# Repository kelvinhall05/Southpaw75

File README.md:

# Southpaw75

The Southpaw75 is a budget FR4 keyboard designed to make a southpaw-style layout available to everyone with as few compromises as possible.

### Disclaimer: You must follow this guide in the order it is written. Assembling stuff in the wrong order (specifically your Pro Micro or Elite C and its headers) will likely result in you having to desolder components and significantly increase the amount of time it takes to assemble. I am not responsible for boards damaged during assembly. I highly recommend you read through the entire guide before starting assembly.

### Please also note that the pictures in this guide were mostly taken after I had already assembled a prototype, and I did not have enough diodes or any switches to fully assemble another board. Please only use the pictures in this guide as a reference for the step they follow and not as the guide itself.

# Assembly:
### This is what the back of an empty PCB looks like (please note, the GB version has some minor changes):

### 1. Bend the legs of all your diodes so they look like this:

### 2. Put the diodes through the PCB so the legs stick out the front side of the board and so the diode is flush with the back, making sure the black line on the diode faces the square pad:

### 3. Solder from the back and snip the legs:

### 4. Repeat for all diodes (you will have to solder 78, and you may have several extras). Please note that several diodes have their footprint rotated but are electrically identical, meaning black stripe will still go to square pad.
### 5. Solder your reset button to the PCB (use tweezers to hold it down, as the metal will conduct heat from your iron and burn your finger)
### Note: If you've lost your reset button, don't worry. Shorting the two pads closest to the edge of the PCB or the two closest to the inside will reset your controller. After all, that's all the button does :)
### 6. Place your Pro Micro or Elite C onto its pin headers and sit it into the board so the Pro Micro is on the back of the PCB (the side with the Southpaw logo) and tape it down to temporarily hold it in place. This helps align the pin headers properly. It doesn't matter whether you put the shorter pins on the PCB or the longer ones; either way, you will have to snip the longer ones once you've soldered them in. **DO NOT SOLDER THE PRO MICRO OR ELITE C TO THE PIN HEADERS YET!**

### 7. Solder in the pin headers from the front side of the PCB. **Do not solder the Pro Micro or Elite C yet, just the headers!**

### 8. Attach your stabs to the PCB (some PCB stabs might be a tight fit with the plate; do not be afraid to push, you won't break it)
### 9. Mount switches in the corner of the plate to align it, then lower the plate onto the PCB
### 10. Add the rest of your switches and solder them all in
### 11. Once you have verified that all your diodes, switches, and Pro Micro or Elite C pin headers are soldered properly, you can now solder your Pro Micro or Elite C onto the pin headers:

### Here is what a completed PCB will look like:

### 12. Attach standoffs to the bottom of the plate using screws from the other side
### 13. Screw on the bottom plate
# Flashing instructions for Linux:
### 1. Plug your Pro Micro or Elite C in
### 2. Open up the [QMK configurator](https://config.qmk.fm/#/southpaw75/LAYOUT) and create your desired layout
### 3. Download the .json file (on the left, next to keymap.json)
### 4. Open up a command line
### 5. Type ```qmk flash /path/to/layout.json``` (obviously replacing the file path with the path to your downloaded layout) and follow any additional instructions
### One thing to note is that you can compile a .hex file on the configurator and flash that with avrdude, however, I prefer the method outlined above.
# Flashing instructions for Windows:
### Please keep in mind that I do not run Windows on my own system and cannot 100% verify this flashing procedure will work or if it requires any other configuration. I highly recommend you check the QMK docs if something is not working. I am unable to help with any flashing problems if you run Windows.
### 1. Plug your Pro Micro or Elite C in
### 2. Open up the [QMK configurator](https://config.qmk.fm/#/southpaw75/LAYOUT) and create your desired layout
### 3. Click "compile" in the upper right, and once it's done, download the .hex by clicking "firmware"
### 4. Open up QMK toolbox and load your downloaded .hex
### 5. Click "flash" and follow any additional instructions

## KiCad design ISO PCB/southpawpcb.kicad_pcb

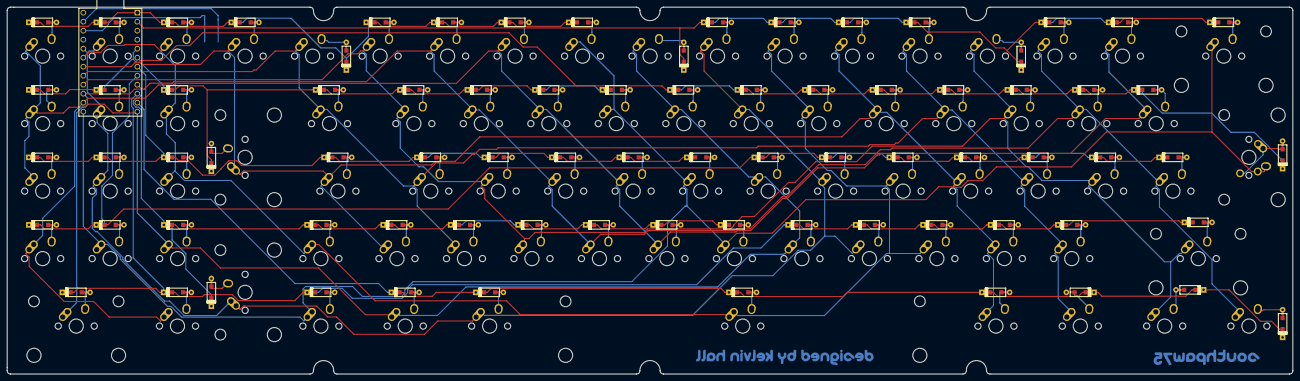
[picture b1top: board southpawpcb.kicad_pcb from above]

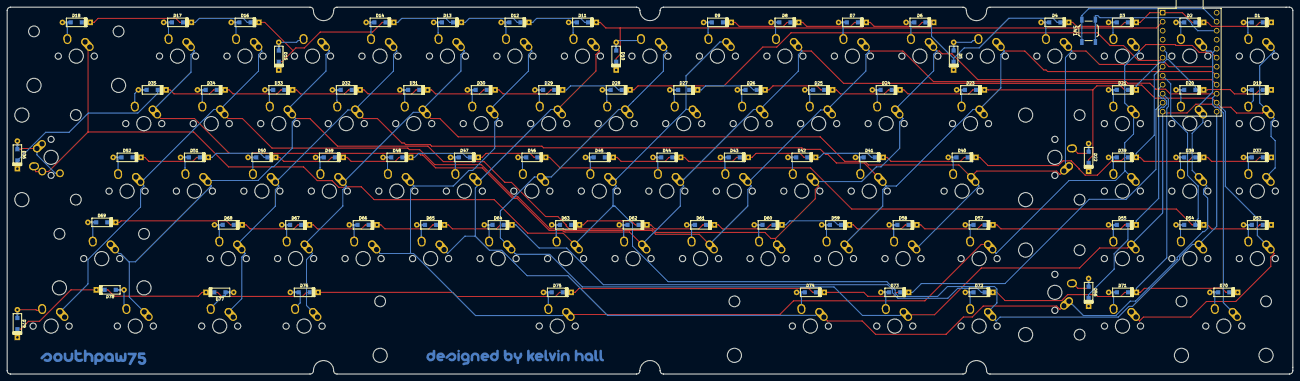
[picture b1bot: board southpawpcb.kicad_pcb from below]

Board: 2 copper layers, 362.9 x 103.6 mm, 164 parts (85 on the bottom side), 99 nets.

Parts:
D1, D2, D3, D4, D5, D6, D7, D8, D9, D10, D11, D12, D13, D14, D15, D16, D17, D18, D19, D20, D21, D22, D23, D24, D25, D26, D27, D28, D29, D30, D31, D32, D33, D34, D35, D36, D37, D38, D39, D40, D41, D42, D43, D44, D45, D46, D47, D48, D49, D50, D51, D52, D53, D54, D55, D56, D57, D58, D59, D60, D61, D62, D63, D64, D65, D66, D67, D68, D69, D70, D71, D72, D73, D74, D75, D76, D77, D78, D79: D; D_SOD123_axial-dual
G1: LOGO; designedbykelvinhallcopy
G2: LOGO; designedbykelvinhall
G3: LOGO; southpaw75smallcopy
G4: LOGO; southpaw75small
K1, K2, K3, K4, K5, K6, K7, K8, K9, K10, K11, K12, K13, K14, K15, K16, K17, K19, K20, K21, K24, K25, K26, K27, K28, K29, K30, K31, K32, K33, K34, K35, K37, K38, K39, K41, K42, K43, K44, K45, K46, K47, K48, K49, K50, K51, K52, K53, K54, K55, K58, K59, K60, K61, K62, K63, K64, K65, K66, K67, K68, K71: KEYSW; MX-1U-NoLED
K18, K22, K56, K70: KEYSW; MX-2U-NoLED
K23: KEYSW; MX-1.5U-NoLED
K36: KEYSW; MX-ISO
K40: KEYSW; MX-1.75U-NoLED
K57, K72, K73, K74, K76, K77, K78, K79: KEYSW; MX-1.25U-NoLED
K69: KEYSW; MX-2.75U-NoLED
K75: KEYSW; MX-6.25U-NoLED
SW1: Reset; SW_SPST_TL3342
U1: ProMicro

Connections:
unnamed: D1.1, D2.1, D3.1, D4.1, D5.1, D6.1, D7.1, D8.1, D9.1, U1.1
unnamed: D1.2, K1.2
unnamed: D2.2, K2.2
unnamed: D3.2, K3.2
unnamed: D4.2, K4.2
unnamed: D5.2, K5.2
unnamed: D6.2, K6.2
unnamed: D7.2, K7.2
unnamed: D8.2, K8.2
unnamed: D9.2, K9.2
unnamed: D10.1, D11.1, D12.1, D13.1, D14.1, D15.1, D16.1, D17.1, D18.1, U1.2
unnamed: D10.2, K10.2
unnamed: D11.2, K11.2
unnamed: D12.2, K12.2
unnamed: D13.2, K13.2
unnamed: D14.2, K14.2
unnamed: D15.2, K15.2
unnamed: D16.2, K16.2
unnamed: D17.2, K17.2
unnamed: D18.2, K18.2
unnamed: D19.1, D20.1, D21.1, D22.1, D23.1, D24.1, D25.1, D26.1, D27.1, U1.5
unnamed: D19.2, K19.2
unnamed: D20.2, K20.2
unnamed: D21.2, K21.2
unnamed: D22.2, K22.2
unnamed: D23.2, K23.2
unnamed: D24.2, K24.2
unnamed: D25.2, K25.2
unnamed: D26.2, K26.2
unnamed: D27.2, K27.2
unnamed: D28.1, D29.1, D30.1, D31.1, D32.1, D33.1, D34.1, D35.1, D36.1, U1.6
unnamed: D28.2, K28.2
unnamed: D29.2, K29.2
unnamed: D30.2, K30.2
unnamed: D31.2, K31.2
unnamed: D32.2, K32.2
unnamed: D33.2, K33.2
unnamed: D34.2, K34.2
unnamed: D35.2, K35.2
unnamed: D36.2, K36.2
unnamed: D37.1, D38.1, D39.1, D40.1, D41.1, D42.1, D43.1, D44.1, D45.1, U1.7
unnamed: D37.2, K37.2
unnamed: D38.2, K38.2
unnamed: D39.2, K39.2
unnamed: D40.2, K40.2
unnamed: D41.2, K41.2
unnamed: D42.2, K42.2
unnamed: D43.2, K43.2
unnamed: D44.2, K44.2
unnamed: D45.2, K45.2
unnamed: D46.1, D47.1, D48.1, D49.1, D50.1, D51.1, D52.1, D53.1, D54.1, U1.8
unnamed: D46.2, K46.2
unnamed: D47.2, K47.2
unnamed: D48.2, K48.2
unnamed: D49.2, K49.2
unnamed: D50.2, K50.2
unnamed: D51.2, K51.2
unnamed: D52.2, K52.2
unnamed: D53.2, K53.2
unnamed: D54.2, K54.2
unnamed: D55.1, D56.1, D57.1, D58.1, D59.1, D60.1, D61.1, D62.1, D63.1, U1.9
unnamed: D55.2, K55.2
unnamed: D56.2, K56.2
unnamed: D57.2, K57.2
unnamed: D58.2, K58.2
unnamed: D59.2, K59.2
unnamed: D60.2, K60.2
unnamed: D61.2, K61.2
unnamed: D62.2, K62.2
unnamed: D63.2, K63.2
unnamed: D64.1, D65.1, D66.1, D67.1, D68.1, D69.1, D70.1, D71.1, D72.1, U1.10
unnamed: D64.2, K64.2
unnamed: D65.2, K65.2
unnamed: D66.2, K66.2
unnamed: D67.2, K67.2
unnamed: D68.2, K68.2
unnamed: D69.2, K69.2
unnamed: D70.2, K70.2
unnamed: D71.2, K71.2
unnamed: D72.2, K72.2
unnamed: D73.1, D74.1, D75.1, D76.1, D77.1, D78.1, D79.1, U1.11
unnamed: D73.2, K73.2
unnamed: D74.2, K74.2
unnamed: D75.2, K75.2
unnamed: D76.2, K76.2
unnamed: D77.2, K77.2
unnamed: D78.2, K78.2
unnamed: D79.2, K79.2
unnamed: K1.1, K10.1, K19.1, K28.1, K37.1, K46.1, K55.1, K64.1, K73.1, U1.12
unnamed: K2.1, K11.1, K20.1, K29.1, K38.1, K47.1, K56.1, K65.1, K74.1, U1.20
unnamed: K3.1, K12.1, K21.1, K30.1, K39.1, K48.1, K57.1, K66.1, K75.1, U1.19
unnamed: K4.1, K13.1, K22.1, K31.1, K40.1, K49.1, K58.1, K67.1, K76.1, U1.18
unnamed: K5.1, K14.1, K23.1, K32.1, K41.1, K50.1, K59.1, K68.1, K77.1, U1.17
unnamed: K6.1, K15.1, K24.1, K33.1, K42.1, K51.1, K60.1, K69.1, K78.1, U1.16
unnamed: K7.1, K16.1, K25.1, K34.1, K43.1, K52.1, K61.1, K70.1, K79.1, U1.15
unnamed: K8.1, K17.1, K26.1, K35.1, K44.1, K53.1, K62.1, K71.1, U1.14
unnamed: K9.1, K18.1, K27.1, K36.1, K45.1, K54.1, K63.1, K72.1, U1.13
unnamed: SW1.1, U1.23
unnamed: SW1.2, U1.22

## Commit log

2020-07-29 Adding Southpaw75 files
2020-07-29 Adding QMK
2020-07-29 Adding pictures folder
2020-08-19 updating QMK and PCBs
2020-08-31 adding pictures for guide
2020-08-31 Add build guide to readme
2020-09-01 Add flashing instructions
2020-09-01 Adding Discord
2020-09-03 Update assembly guide
2020-09-03 Update flashing guide
2020-09-06 Update build guide
2020-12-09 Added iso QMK and Via files
2021-03-13 Adding a license
2021-09-15 Fixing missing libraries, redrawing schematic
